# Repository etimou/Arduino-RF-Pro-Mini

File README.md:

# Arduino-RF-Pro-Mini
**Arduino Pro Mini + nRF24L01P = Arduino-RF-Pro-Mini**
- designed with [Kicad](https://kicad.org/).
- 100% Arduino Pro Mini pin compatible
- embeds nRF24l01+ chip for radio communication
- low power (can run for months on a battery)
- compatible with [MySensors](www.mysensors.org) framework, but not only

**Programming the board**

You need to select Arduino Pro or Pro mini, ATmega328P (3.3V, 8MHz) in the Arduino IDE. An USB-Serial adapter that provides 3.3V is required, otherwise the radio chip can be damaged.

**Source code**

The example program consists in a roundtrip message that is sent from a node, using a gateway. You need two modules.

**Special thanks**

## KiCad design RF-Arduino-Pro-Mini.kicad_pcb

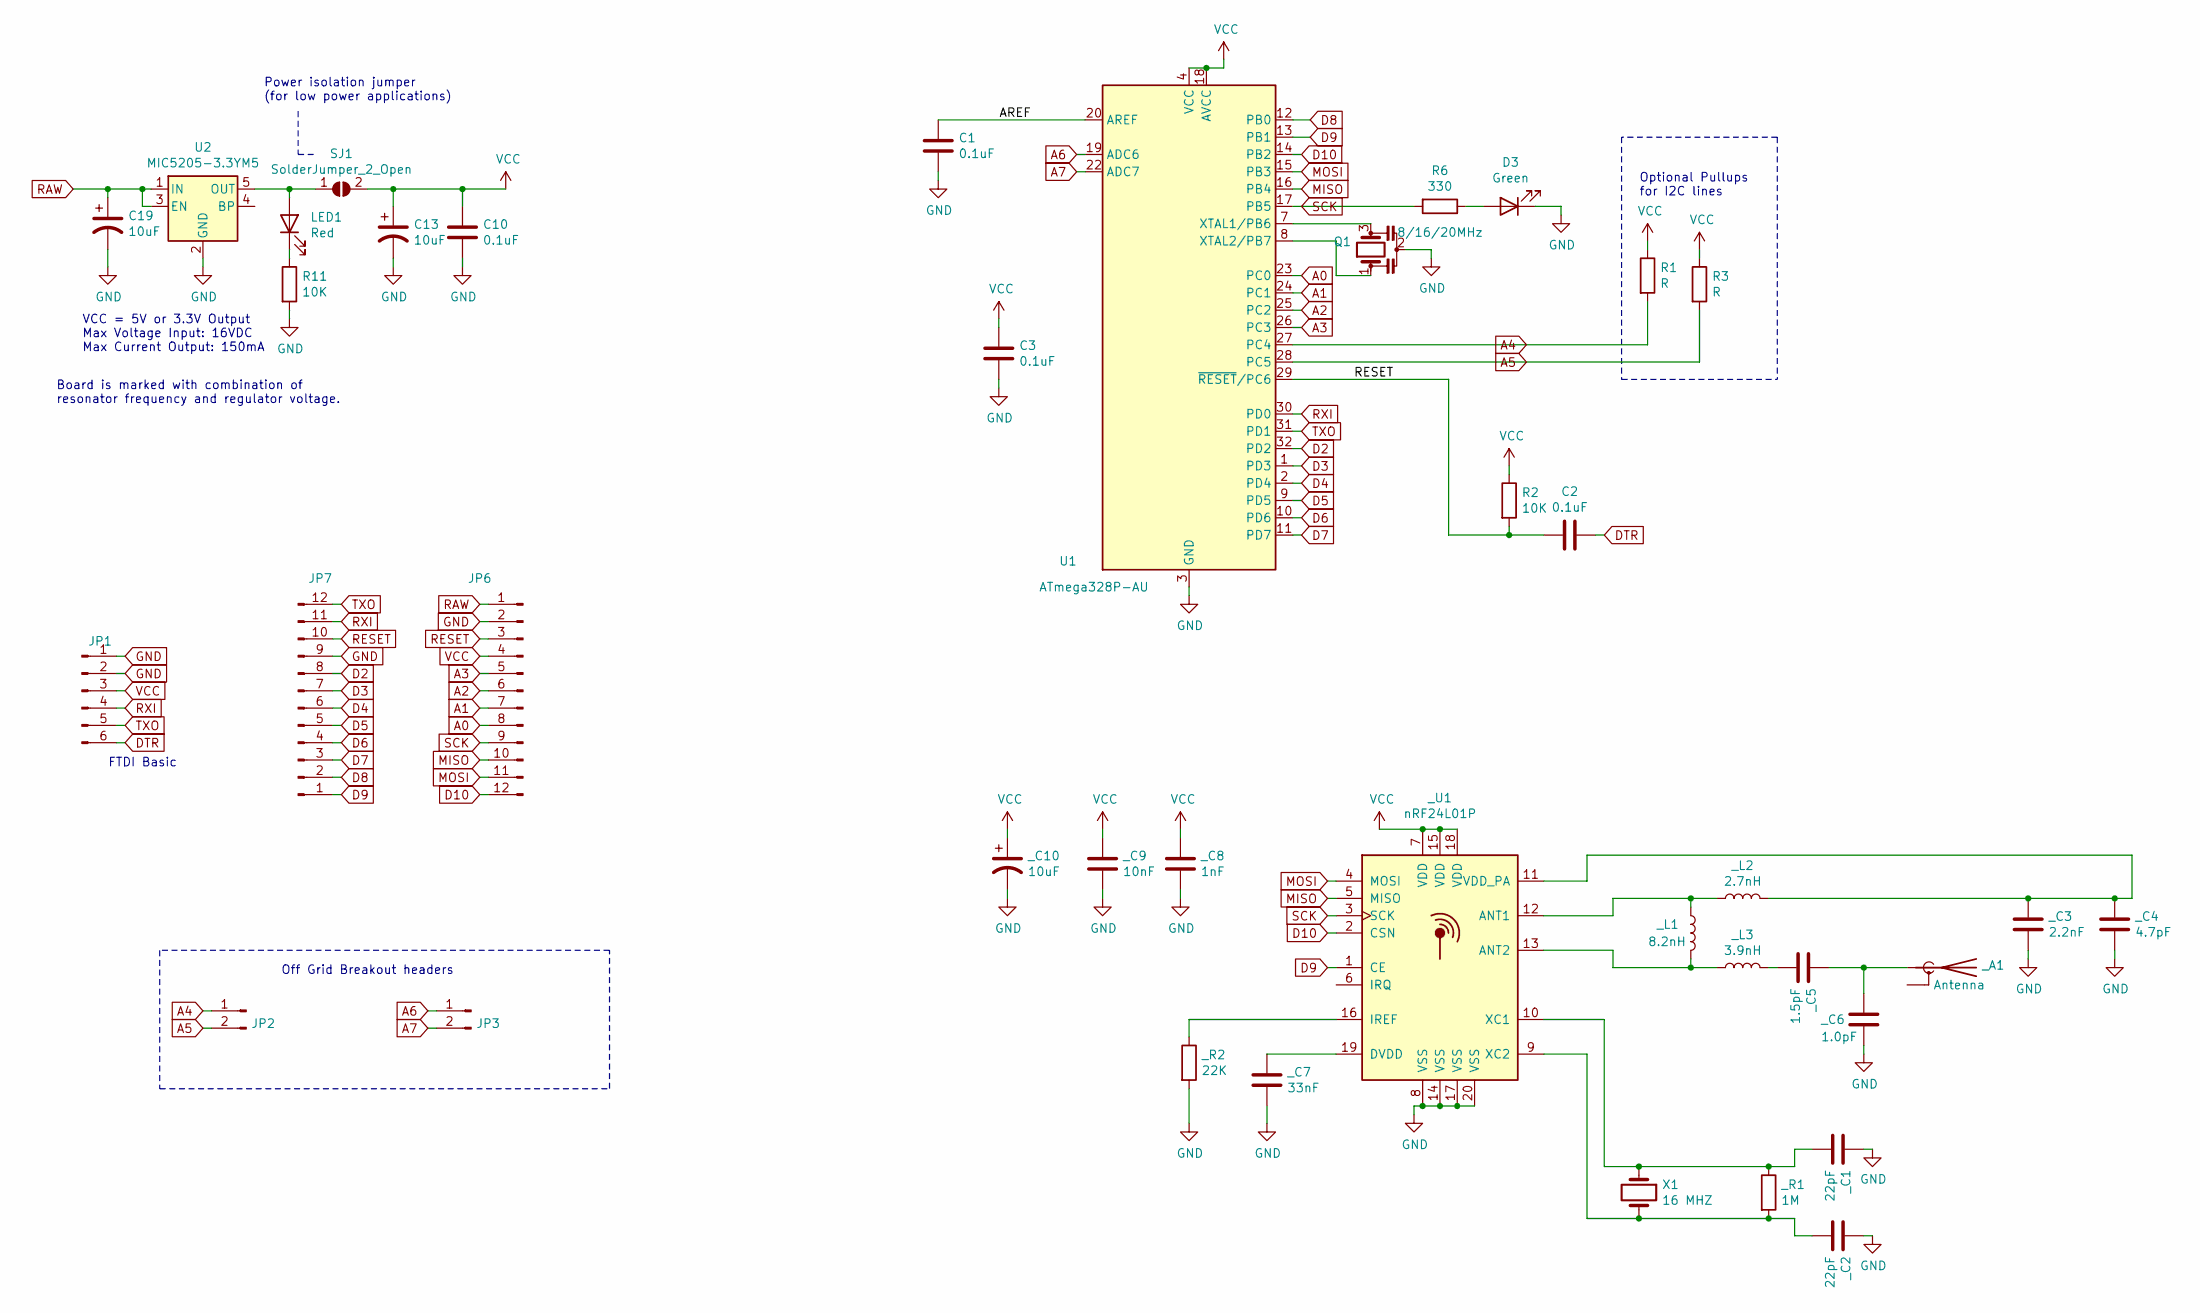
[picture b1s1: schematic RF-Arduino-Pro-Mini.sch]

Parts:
C1, C2, C3, C10: 0.1uF; C_0603_1608Metric
C13, C19: 10uF; C_1206_3216Metric
D3: Green; LED_0603_1608Metric
JP1: Conn_01x06_Male; PinHeader_1x06_P2.54mm_Vertical
JP2, JP3: Conn_01x02_Male; PinHeader_1x02_P2.54mm_Vertical
JP6, JP7: Conn_01x12_Male; PinHeader_1x12_P2.54mm_Vertical
LED1: Red; LED_0603_1608Metric
Q1: 8/16/20MHz; Resonator_SMD_muRata_CSTxExxV-3Pin_3.0x1.1mm
R1, R3: R; R_0603_1608Metric
R2, R11: 10K; R_0603_1608Metric
R6: 330; R_0603_1608Metric
SJ1: SolderJumper_2_Open; SolderJumper-2_P1.3mm_Open_Pad1.0x1.5mm
U1: ATmega328P-AU; TQFP-32_7x7mm_P0.8mm
U2: MIC5205-3.3YM5; SOT-23-5
X1: 16 MHZ; Crystal_SMD_5032-2Pin_5.0x3.2mm
_A1: Antenna; ANT-2.45-CHP
_C1, _C2: 22pF; C_0402_1005Metric
_C3: 2.2nF; C_0402_1005Metric
_C4: 4.7pF; C_0402_1005Metric
_C5: 1.5pF; C_0402_1005Metric
_C6: 1.0pF; C_0402_1005Metric
_C7: 33nF; C_0402_1005Metric
_C8: 1nF; C_0402_1005Metric
_C9: 10nF; C_0402_1005Metric
_C10: 10uF; C_1206_3216Metric
_L1: 8.2nH; L_0402_1005Metric
_L2: 2.7nH; L_0402_1005Metric
_L3: 3.9nH; L_0402_1005Metric
_R1: 1M; R_0402_1005Metric
_R2: 22K; R_0402_1005Metric
_U1: nRF24L01P; QFN-20-1EP_4x4mm_P0.5mm_EP2.5x2.5mm

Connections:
/AREF: C1.1, U1.20 (AREF)
A0: JP6.8, U1.23 (PC0)
A1: JP6.7, U1.24 (PC1)
A2: JP6.6, U1.25 (PC2)
A3: JP6.5, U1.26 (PC3)
A4: JP2.1, R1.2, U1.27 (PC4)
A5: JP2.2, R3.2, U1.28 (PC5)
A6: JP3.1, U1.19 (ADC6)
A7: JP3.2, U1.22 (ADC7)
D2: JP7.8, U1.32 (PD2)
D3: JP7.7, U1.1 (PD3)
D4: JP7.6, U1.2 (PD4)
D5: JP7.5, U1.9 (PD5)
D6: JP7.4, U1.10 (PD6)
D7: JP7.3, U1.11 (PD7)
D8: JP7.2, U1.12 (PB0)
D9: JP7.1, U1.13 (PB1), _U1.1 (CE)
D10: JP6.12, U1.14 (PB2), _U1.2 (CSN)
DTR: C2.1, JP1.6
GND: C1.2, C3.2, C10.2, C13.2, C19.2, D3.1 (K), JP1.1, JP1.2, JP6.2, JP7.9, Q1.2, R11.2, U1.3 (GND), U1.5 (GND), U1.21 (GND), U2.2 (GND), _C1.1, _C2.1, _C3.2, _C4.2, _C6.2, _C7.2, _C8.2, _C9.2, _C10.2, _R2.2, _U1.8 (VSS), _U1.14 (VSS), _U1.17 (VSS), _U1.20 (VSS)
MISO: JP6.10, U1.16 (PB4), _U1.5 (MISO)
MOSI: JP6.11, U1.15 (PB3), _U1.4 (MOSI)
unnamed: D3.2 (A), R6.1
unnamed: LED1.1 (K), R11.1
unnamed: LED1.2 (A), SJ1.1 (A), U2.5 (OUT)
unnamed: Q1.1, U1.8 (XTAL2/PB7)
unnamed: Q1.3, U1.7 (XTAL1/PB6)
unnamed: X1.1, _C1.2, _R1.1, _U1.10 (XC1)
unnamed: X1.2, _C2.2, _R1.2, _U1.9 (XC2)
unnamed: _A1.1 (A), _C5.1, _C6.1
unnamed: _C3.1, _C4.1, _L2.2, _U1.11 (VDD_PA)
unnamed: _C5.2, _L3.2
unnamed: _C7.1, _U1.19 (DVDD)
unnamed: _L1.1, _L2.1, _U1.12 (ANT1)
unnamed: _L1.2, _L3.1, _U1.13 (ANT2)
unnamed: _R2.1, _U1.16 (IREF)
RAW: C19.1, JP6.1, U2.1 (IN), U2.3 (EN)
RESET: C2.2, JP6.3, JP7.10, R2.2, U1.29 (~RESET~/PC6)
RXI: JP1.4, JP7.11, U1.30 (PD0)
SCK: JP6.9, R6.2, U1.17 (PB5), _U1.3 (SCK)
TXO: JP1.5, JP7.12, U1.31 (PD1)
VCC: C3.1, C10.1, C13.1, JP1.3, JP6.4, R1.1, R2.1, R3.1, SJ1.2 (B), U1.4 (VCC), U1.6 (VCC), U1.18 (AVCC), _C8.1, _C9.1, _C10.1, _U1.7 (VDD), _U1.15 (VDD), _U1.18 (VDD)

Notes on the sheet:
Off Grid Breakout headers
Optional Pullups for I2C lines
FTDI Basic
Power isolation jumper (for low power applications)
VCC = 5V or 3.3V Output Max Voltage Input: 16VDC Max Current Output: 150mA
Board is marked with combination of resonator frequency and regulator voltage.

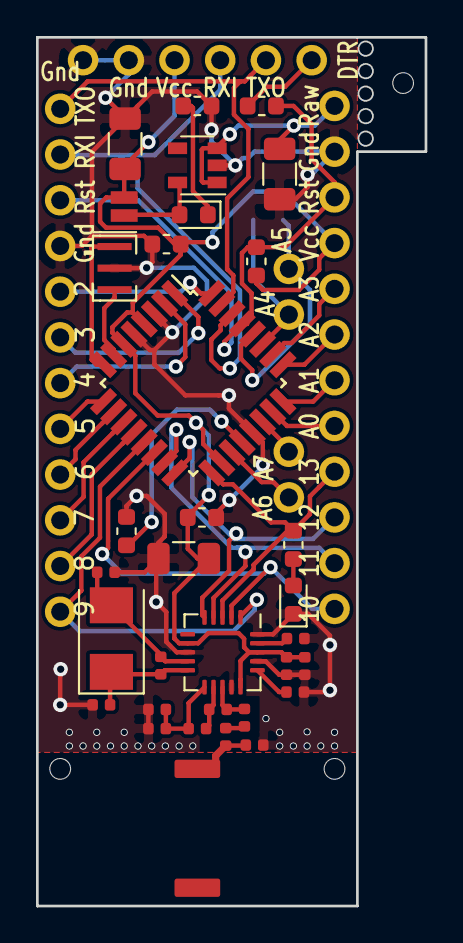
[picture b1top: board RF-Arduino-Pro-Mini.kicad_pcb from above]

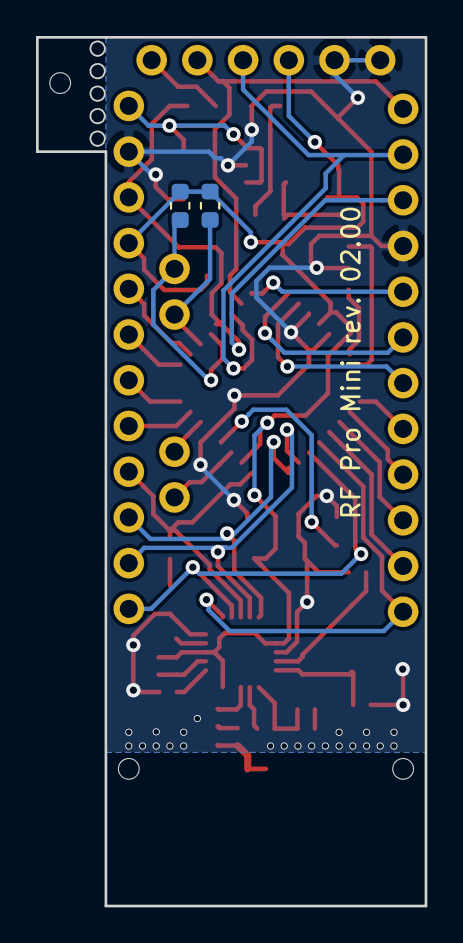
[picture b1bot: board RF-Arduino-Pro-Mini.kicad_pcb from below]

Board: 2 copper layers, 21.6 x 48.3 mm, 40 parts (2 on the bottom side), 42 nets.

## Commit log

2020-04-24 initial
2020-08-16 first update after v1 release
2020-08-16 add files
2020-08-16 Readme update
2021-11-08 Update README.md
    https://forum.kicad.info/t/warning-avoid-all-links-to-kicad-pcb-org-use-kicad-org/31521
